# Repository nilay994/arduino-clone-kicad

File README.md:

# Expt. with KiCad

https://www.udemy.com/course/kicad-like-a-pro-2e
- installing libraries for symbols and footprints (good source: digikey and Angus's)
- steps (maybe subject to copyright)

## This is a deep-copy of the BACEE project by futureshocked
URL: https://github.com/futureshocked/KicadLikeAPro-Project-3-BACEE
This repository doesn't claim that the schema or pcb designed is functional. The function of these files is purely for experimenting with KiCad.

## List of components
1. battery
2. pol cap + cer cap
3. LED
4. conn 01x09
5. conn 01x04
6. conn 02x03
7. conn 01x04
8. 2x resist
9. i2c eeprom
10. AtMega 328
11. Clock

## Good practice:
Use gerblook.org for viewing the individual layers and check outer edgecut dimension.
Upload gerber to PCBWay to check the prices of 2/4 layer to get an estimate.

## Autorouter
`FreeRouting.jar` using java runtime, copy the executable to the project directory.
https://layouteditor.com/download: could do 2 and 4 layers: no problems passing DRC. 

## Failure
1. With autorouter: critical aspects of differential pair routing, power emi noise are not ensured.
2. Signal and power tracks might be running close due to autorouting.
3. components and mounting hole alignment is not optimal, manufacturer drill, via, silk, min track gap compatibility is not ensured.
4. footprint cross check not done.
5. schema has no way to ensure safety of Atmega: no power reg, no diodes or fuse..
6. not the best connectors are used, use screw terminal for power: check courtyard and physical clearance.
7. i2c/pullup termination line capacitance not ensured.
8. silkscreen instructions are sparse like IC notch.
9. XTAL tracks are not the same length!!
10. LED is on SCK line, loading effect not known.
11. PCB could be smaller, some tracks could be self-routed.

## current render

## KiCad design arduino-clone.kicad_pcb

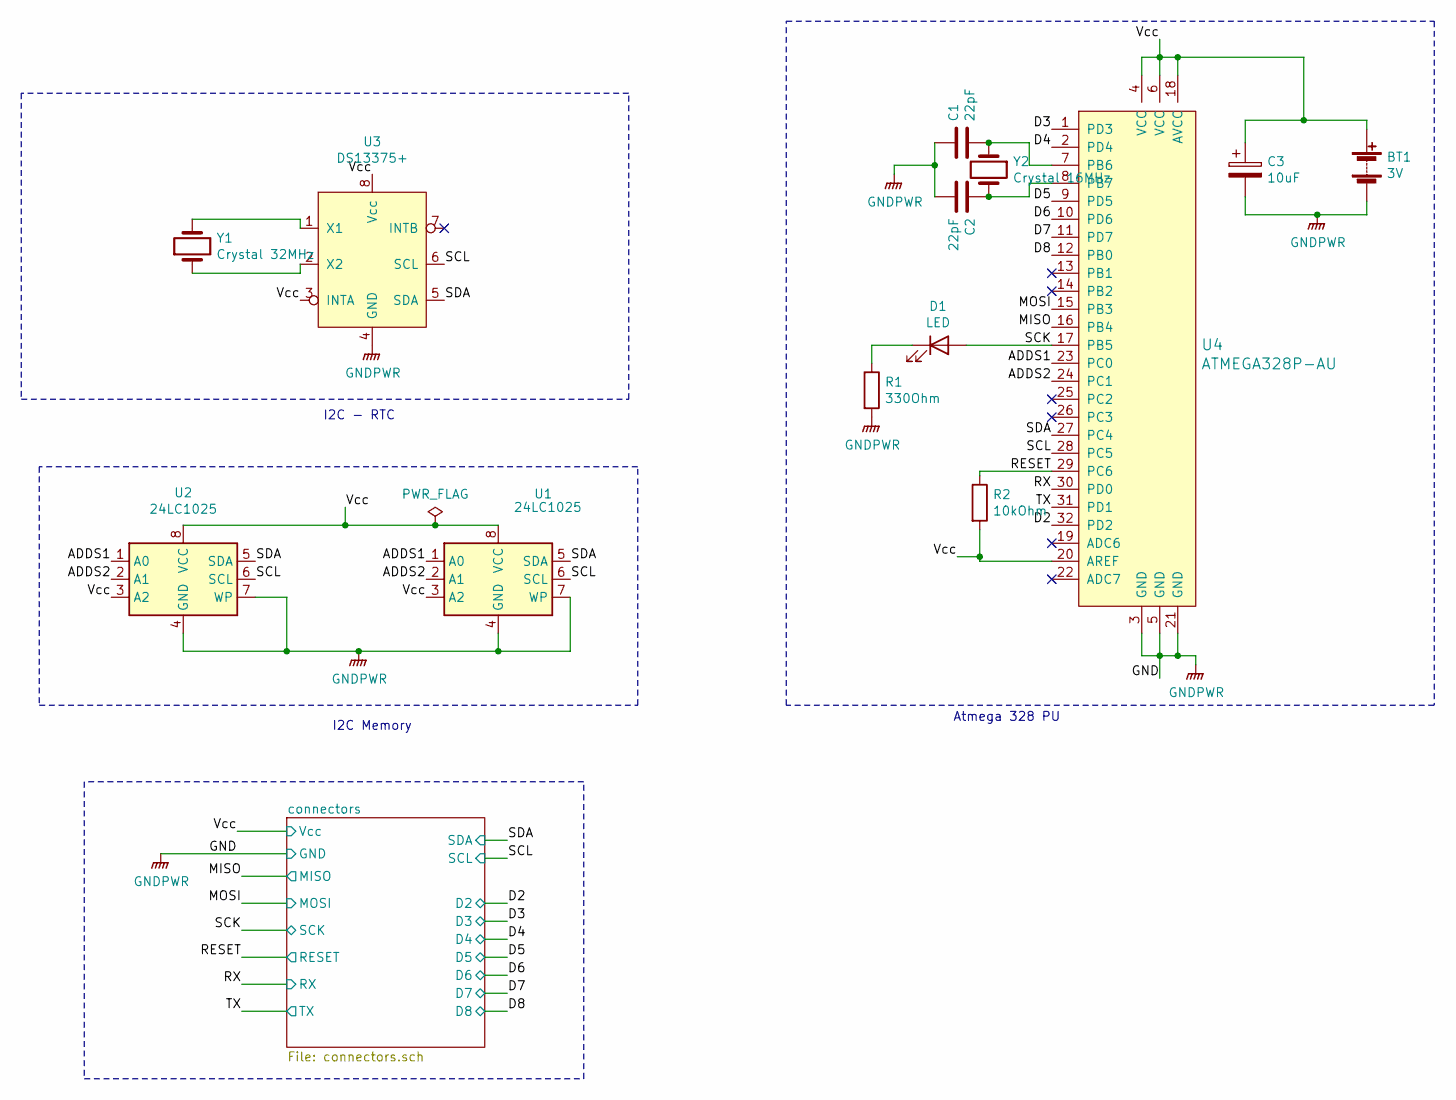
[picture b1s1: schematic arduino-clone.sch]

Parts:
BT1: 3V; PinHeader_1x02_P2.54mm_Vertical
C1, C2: 22pF; C_0805_2012Metric_Pad1.15x1.40mm_HandSolder
C3: 10uF; C_0805_2012Metric_Pad1.15x1.40mm_HandSolder
D1: LED; LED_0805_2012Metric_Pad1.15x1.40mm_HandSolder
R1: 330Ohm; R_0805_2012Metric_Pad1.15x1.40mm_HandSolder
R2: 10kOhm; R_0805_2012Metric_Pad1.15x1.40mm_HandSolder
U1, U2: 24LC1025; SOIJ-8_5.3x5.3mm_P1.27mm
U3: DS13375+; SO-8_5.3x6.2mm_P1.27mm
U4: ATMEGA328P-AU; TQFP-32_7x7mm; MPN ATMEGA328P-AU; Digi-Key_PN ATMEGA328P-AU-ND
Y1: Crystal 32MHz; Crystal_SMD_MicroCrystal_CC7V-T1A-2Pin_3.2x1.5mm_HandSolder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
Y2: Crystal 16MHz; Crystal_SMD_MicroCrystal_CC7V-T1A-2Pin_3.2x1.5mm_HandSolder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

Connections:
/ADDS1: U1.1 (A0), U2.1 (A0), U4.23 (PC0)
/ADDS2: U1.2 (A1), U2.2 (A1), U4.24 (PC1)
/D2: U4.32 (PD2); also elsewhere on the board
/D3: U4.1 (PD3); also elsewhere on the board
/D4: U4.2 (PD4); also elsewhere on the board
/D5: U4.9 (PD5); also elsewhere on the board
/D6: U4.10 (PD6); also elsewhere on the board
/D7: U4.11 (PD7); also elsewhere on the board
/D8: U4.12 (PB0); also elsewhere on the board
/MISO: U4.16 (PB4); also elsewhere on the board
/MOSI: U4.15 (PB3); also elsewhere on the board
/RESET: R2.1, U4.29 (PC6); also elsewhere on the board
/RX: U4.30 (PD0); also elsewhere on the board
/SCK: D1.2 (A), U4.17 (PB5); also elsewhere on the board
/SCL: U1.6 (SCL), U2.6 (SCL), U3.6 (SCL), U4.28 (PC5); also elsewhere on the board
/SDA: U1.5 (SDA), U2.5 (SDA), U3.5 (SDA), U4.27 (PC4); also elsewhere on the board
/TX: U4.31 (PD1); also elsewhere on the board
/Vcc: BT1.1 (+), C3.1, R2.2, U1.3 (A2), U1.8 (VCC), U2.3 (A2), U2.8 (VCC), U3.3 (INTA), U3.8 (Vcc), U4.4 (VCC), U4.6 (VCC), U4.18 (AVCC), U4.20 (AREF); also elsewhere on the board
GNDPWR: BT1.2 (-), C1.1, C2.2, C3.2, R1.2, U1.4 (GND), U1.7 (WP), U2.4 (GND), U2.7 (WP), U3.4 (GND), U4.3 (GND), U4.5 (GND), U4.21 (GND); also elsewhere on the board
unnamed: C1.2, U4.7 (PB6), Y2.1
unnamed: C2.1, U4.8 (PB7), Y2.2
unnamed: D1.1 (K), R1.1
unnamed: U3.1 (X1), Y1.2
unnamed: U3.2 (X2), Y1.1

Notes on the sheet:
Atmega 328 PU
I2C Memory
I2C - RTC

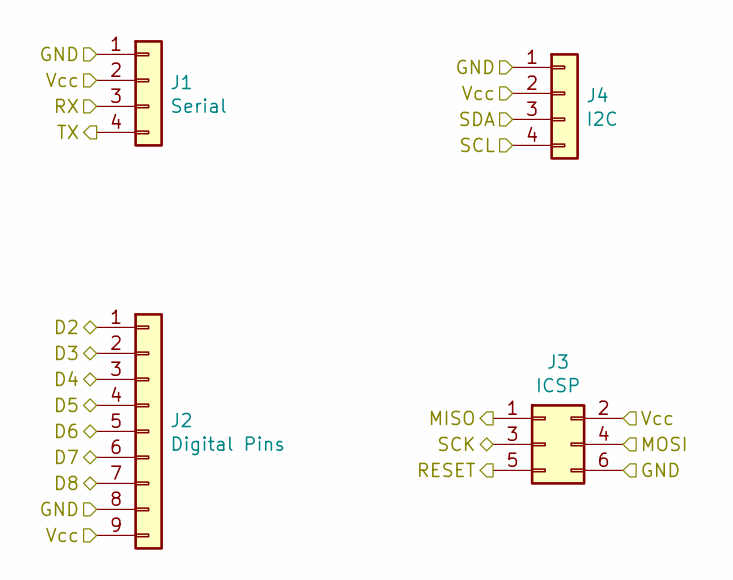
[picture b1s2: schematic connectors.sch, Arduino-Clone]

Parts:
J1: Serial; PinHeader_1x04_P2.54mm_Vertical
J2: Digital Pins; PinHeader_1x09_P2.54mm_Vertical
J3: ICSP; PinHeader_2x03_P2.54mm_Vertical
J4: I2C; PinHeader_1x04_P2.54mm_Vertical

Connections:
/D2: J2.1; also elsewhere on the board
/D3: J2.2; also elsewhere on the board
/D4: J2.3; also elsewhere on the board
/D5: J2.4; also elsewhere on the board
/D6: J2.5; also elsewhere on the board
/D7: J2.6; also elsewhere on the board
/D8: J2.7; also elsewhere on the board
/MISO: J3.1; also elsewhere on the board
/MOSI: J3.4; also elsewhere on the board
/RESET: J3.5; also elsewhere on the board
/RX: J1.3; also elsewhere on the board
/SCK: J3.3; also elsewhere on the board
/SCL: J4.4; also elsewhere on the board
/SDA: J4.3; also elsewhere on the board
/TX: J1.4; also elsewhere on the board
/Vcc: J1.2, J2.9, J3.2, J4.2; also elsewhere on the board
GNDPWR: J1.1, J2.8, J3.6, J4.1; also elsewhere on the board

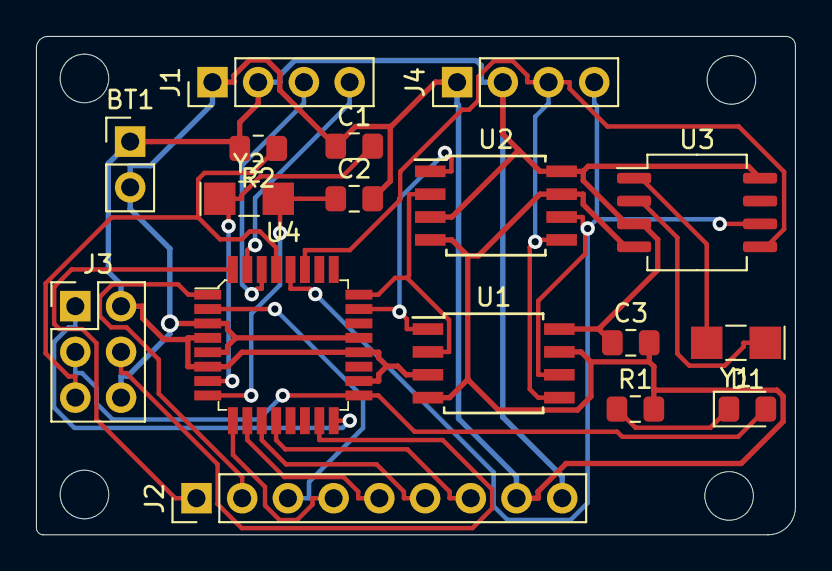
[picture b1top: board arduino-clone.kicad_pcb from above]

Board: 4 copper layers, 42.2 x 27.7 mm, 17 parts (0 on the bottom side), 24 nets.

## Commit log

2020-06-14 [eeschema] add init files
2020-06-14 [eeschema] add heir sheet, associate footprints
2020-06-16 [eeshema] assign values, connect symbols
2020-06-16 [pcbnew] add 2 and 4 layer autorouted pcbs
2020-06-16 [pcbnew] add silk, add render
2020-06-16 [material] add steps
2020-06-16 [misc] re-arrange
